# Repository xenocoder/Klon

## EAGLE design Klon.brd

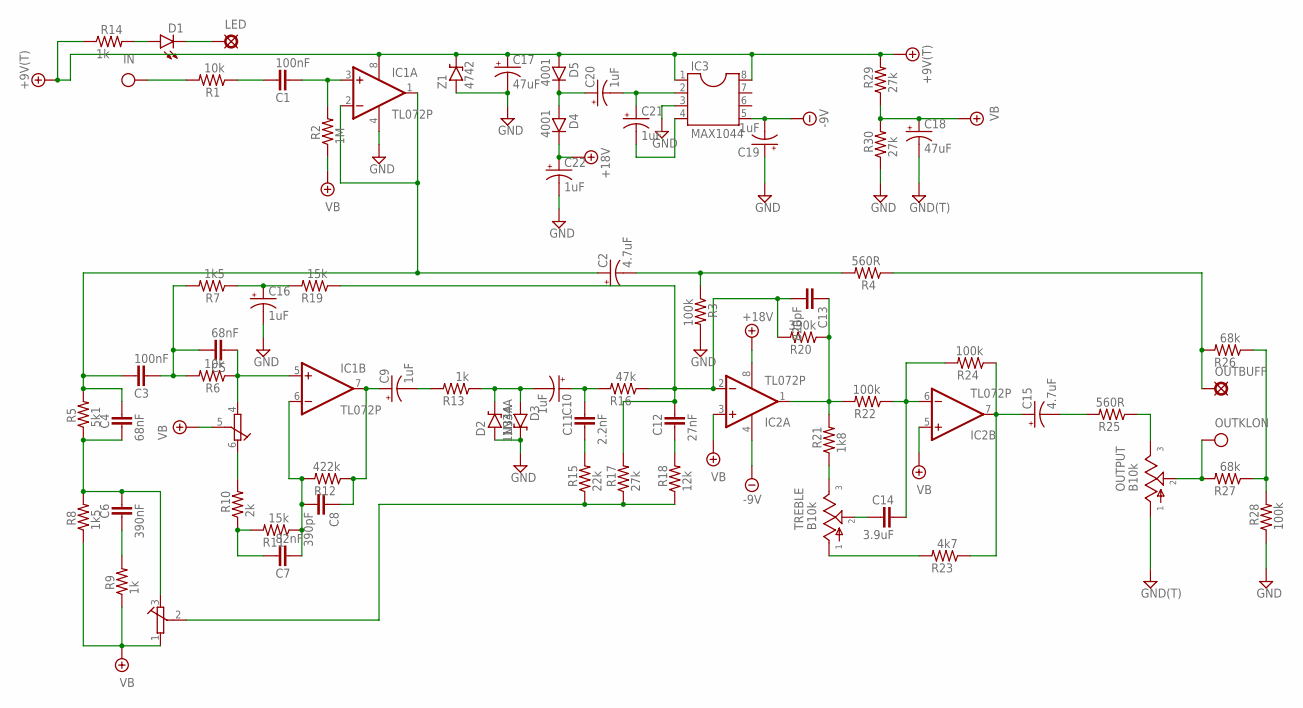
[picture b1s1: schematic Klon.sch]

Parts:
+9V, +9V1: +9V(T); SQUARE
C1, C3: 100nF; 072X025
C2, C15: 4.7uF; 050_020_1
C4, C5: 68nF; 072X025
C6: 390nF; 072X025
C7: 82nF; 072X025
C8: 390pF; 050X030_025
C9, C10, C16, C19, C20, C21, C22: 1uF; 050_020_1
C11: 2.2nF; 072X025
C12: 27nF; 072X025
C13: 820pF; 050X030_025
C14: 3.9uF; 072X025
C17, C18: 47uF; 063_025
D1: LED; LED3MM
D2, D3: 1N34A; DO35-3
D4, D5: 4001; DO41-3
G, G1: GND(T); SQUARE
GAIN: B100k; ALPHA16MM
IC1, IC2: TL072P; DIL08
IC3: MAX1044; DIL08
IN: IN(T); SQUARE
LED: PAD; SQUARE
OUTBUFF: PAD; SQUARE
OUTKLON: OUT(T); SQUARE
OUTPUT: B10k; 16MM
R1, R6: 10k; R0207/3
R2: 1M; R0207/3
R3, R22, R24, R28: 100k; R0207/3
R4, R25: 560R; R0207/3
R5: 5k1; R0207/3
R7, R8: 1k5; R0207/3
R9, R13, R14: 1k; R0207/3
R10: 2k; R0207/3
R11, R19: 15k; R0207/3
R12: 422k; R0207/3
R15: 22k; R0207/3
R16: 47k; R0207/3
R17, R29, R30: 27k; R0207/3
R18: 12k; R0207/3
R20: 390k; R0207/3
R21: 1k8; R0207/3
R23: 4k7; R0207/3
R26, R27: 68k; R0207/3
TREBLE: B10k; 16MM
Z1: 4742; DO41-3

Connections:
+9V: +9V.1, +9V1.1, C17.+, D5.A, IC1.8 (V+), IC3.1, IC3.8, R14.1, R29.2, Z1.C
+18V: C22.+, D4.C, IC2.8 (V+)
-9V: C19.-, IC2.4 (V-), IC3.5
GND: C16.-, C17.-, C18.-, C19.+, C22.-, D2.A, D3.C, G.1, G1.1, IC1.4 (V-), IC3.3, OUTPUT.1, R3.2, R28.1, R30.1, Z1.A
IN: IN.1, R1.2
unnamed: C2.-, R3.1, R4.2
unnamed: D1.K (C), LED.1
unnamed: D1.A, R14.2
unnamed: C20.+, D4.A, D5.C
unnamed: C2.+, C3.2, C4.2, IC1.1 (OUT), IC1.2 (-IN), R5.2
unnamed: C21.-, IC3.4
unnamed: C13.1, IC2.1 (OUT), R20.1, R21.2, R22.2
unnamed: C6.1, R9.2
unnamed: OUTBUFF.1, R4.1, R26.2
unnamed: C1.2, R1.1
unnamed: C1.1, IC1.3 (+IN), R2.2
unnamed: C4.1, C6.2, GAIN.3 (IN), R5.1, R8.2
unnamed: C9.-, R13.2
unnamed: C3.1, C5.2, R6.2, R7.2
unnamed: C16.+, R7.1, R19.2
unnamed: C5.1, GAIN.4 (GND), IC1.5 (+IN), R6.1
unnamed: GAIN.6 (IN), R10.2
unnamed: C7.2, R10.1, R11.2
unnamed: C7.1, C8.2, IC1.6 (-IN), R11.1, R12.2
unnamed: C8.1, C9.+, IC1.7 (OUT), R12.1
unnamed: C10.-, D2.C, D3.A, R13.1
unnamed: R21.1, TREBLE.3
unnamed: C10.+, C11.2, R16.2
unnamed: C11.1, R15.2
unnamed: C12.2, C13.2, IC2.2 (-IN), R16.1, R17.2, R19.1, R20.2
unnamed: GAIN.2 (OUT), R15.1, R17.1, R18.1
unnamed: C12.1, R18.2
unnamed: C14.1, TREBLE.2
unnamed: C14.2, IC2.6 (-IN), R22.1, R24.2
unnamed: R23.2, TREBLE.1
unnamed: C15.+, IC2.7 (OUT), R23.1, R24.1
unnamed: C15.-, R25.2
unnamed: OUTPUT.3, R25.1
unnamed: C20.-, C21.+, IC3.2
unnamed: R26.1, R27.1, R28.2
OUT: OUTKLON.1, OUTPUT.2, R27.2
VB: C18.+, GAIN.1 (GND), GAIN.5 (OUT), IC2.3 (+IN), IC2.5 (+IN), R2.1, R8.1, R9.1, R29.1, R30.2

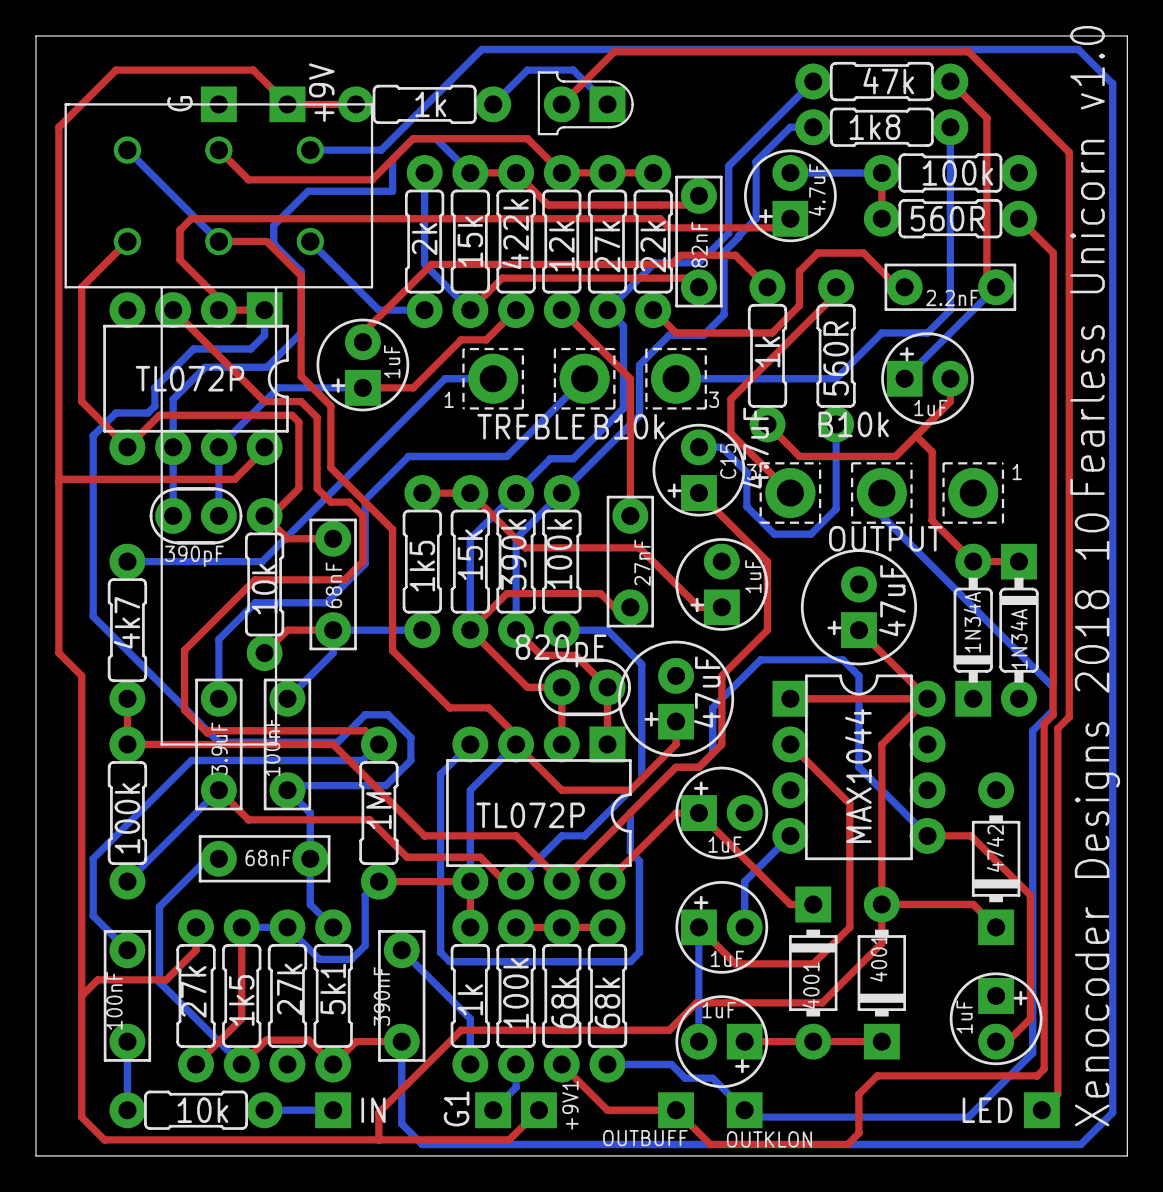
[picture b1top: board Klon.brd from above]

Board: 2 copper layers, 60.6 x 62.2 mm, 72 parts (0 on the bottom side), 42 nets.

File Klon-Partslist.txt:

Partlist

Exported from Klon.sch at 12/17/18 8:35 PM

EAGLE Version 9.2.2 Copyright (c) 1988-2018 Autodesk, Inc.

Assembly variant: 

Part     Value          Device       Package     Library         Sheet

+9V      +9V(T)         +9V(T)       SQUARE      mb_supply       1
+9V1     +9V(T)         +9V(T)       SQUARE      mb_supply       1
C1       100nF          072X0252     072X025     mb_caps-box     1
C2       4.7uF          0501         050_020_1   mb_caps-electro 1
C3       100nF          072X0252     072X025     mb_caps-box     1
C4       68nF           072X0252     072X025     mb_caps-box     1
C5       68nF           072X0252     072X025     mb_caps-box     1
C6       390nF          072X0252     072X025     mb_caps-box     1
C7       82nF           072X0252     072X025     mb_caps-box     1
C8       390pF          050X030_0251 050X030_025 mb_caps-ceramic 1
C9       1uF            0501         050_020_1   mb_caps-electro 1
C10      1uF            0501         050_020_1   mb_caps-electro 1
C11      2.2nF          072X0252     072X025     mb_caps-box     1
C12      27nF           072X0252     072X025     mb_caps-box     1
C13      820pF          050X030_0251 050X030_025 mb_caps-ceramic 1
C14      3.9uF          072X0252     072X025     mb_caps-box     1
C15      4.7uF          0501         050_020_1   mb_caps-electro 1
C16      1uF            0501         050_020_1   mb_caps-electro 1
C17      47uF           0631         063_025     mb_caps-electro 1
C18      47uF           0631         063_025     mb_caps-electro 1
C19      1uF            0501         050_020_1   mb_caps-electro 1
C20      1uF            0501         050_020_1   mb_caps-electro 1
C21      1uF            0501         050_020_1   mb_caps-electro 1
C22      1uF            0501         050_020_1   mb_caps-electro 1
D1       LED            LED3MM       LED3MM      mb_diodes       1
D2       1N34A          1N9ZENER     DO35-3      mb_diodes       1
D3       1N34A          1N9ZENER     DO35-3      mb_diodes       1
D4       4001           1N400X.3     DO41-3      mb_diodes       1
D5       4001           1N400X.3     DO41-3      mb_diodes       1
G        GND(T)         GND(T)       SQUARE      mb_supply       1
G1       GND(T)         GND(T)       SQUARE      mb_supply       1
GAIN     B100k          ALPHA16MM    ALPHA16MM   Pots - custom   1
IC1      TL072P         TL072P       DIL08       mb_ics          1
IC2      TL072P         TL072P       DIL08       mb_ics          1
IC3      MAX1044        MAX1044      DIL08       mb_ics          1
IN       IN(T)          IN(T)        SQUARE      mb_supply       1
LED                     PAD          SQUARE      mb_supply       1
OUTBUFF                 PAD          SQUARE      mb_supply       1
OUTKLON  OUT(T)         OUT(T)       SQUARE      mb_supply       1
OUTPUT   B10k           POT16MM      16MM        mb_pots         1
R1       10k            6MM.3        R0207/3     mb_resistors    1
R2       1M             6MM.3        R0207/3     mb_resistors    1
R3       100k           6MM.3        R0207/3     mb_resistors    1
R4       560R           6MM.3        R0207/3     mb_resistors    1
R5       5k1            6MM.3        R0207/3     mb_resistors    1
R6       10k            6MM.3        R0207/3     mb_resistors    1
R7       1k5            6MM.3        R0207/3     mb_resistors    1
R8       1k5            6MM.3        R0207/3     mb_resistors    1
R9       1k             6MM.3        R0207/3     mb_resistors    1
R10      2k             6MM.3        R0207/3     mb_resistors    1
R11      15k            6MM.3        R0207/3     mb_resistors    1
R12      422k           6MM.3        R0207/3     mb_resistors    1
R13      1k             6MM.3        R0207/3     mb_resistors    1
R14      1k             6MM.3        R0207/3     mb_resistors    1
R15      22k            6MM.3        R0207/3     mb_resistors    1
R16      47k            6MM.3        R0207/3     mb_resistors    1
R17      27k            6MM.3        R0207/3     mb_resistors    1
R18      12k            6MM.3        R0207/3     mb_resistors    1
R19      15k            6MM.3        R0207/3     mb_resistors    1
R20      390k           6MM.3        R0207/3     mb_resistors    1
R21      1k8            6MM.3        R0207/3     mb_resistors    1
R22      100k           6MM.3        R0207/3     mb_resistors    1
R23      4k7            6MM.3        R0207/3     mb_resistors    1
R24      100k           6MM.3        R0207/3     mb_resistors    1
R25      560R           6MM.3        R0207/3     mb_resistors    1
R26      68k            6MM.3        R0207/3     mb_resistors    1
R27      68k            6MM.3        R0207/3     mb_resistors    1
R28      100k           6MM.3        R0207/3     mb_resistors    1
R29      27k            6MM.3        R0207/3     mb_resistors    1
R30      27k            6MM.3        R0207/3     mb_resistors    1
TREBLE   B10k           POT16MM      16MM        mb_pots         1
Z1       4742           1N47XX3      DO41-3      mb_diodes       1

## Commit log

2018-10-13 First push of Klon files
2018-11-17 Seeed Studio files
2018-11-24 Files for Seeed Studio
2018-12-12 Files to Seeed Studio for v1.0
2019-12-25 Added partslist
